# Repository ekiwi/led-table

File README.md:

8x8 RGB LED Table
=================

This project aimed at creating a 8x8 RGB LED Table that
features two controlers:
* a Colorduino from iTead Studio inside the table
* and a custom Main Board featuring an atmega644
  for the control panel

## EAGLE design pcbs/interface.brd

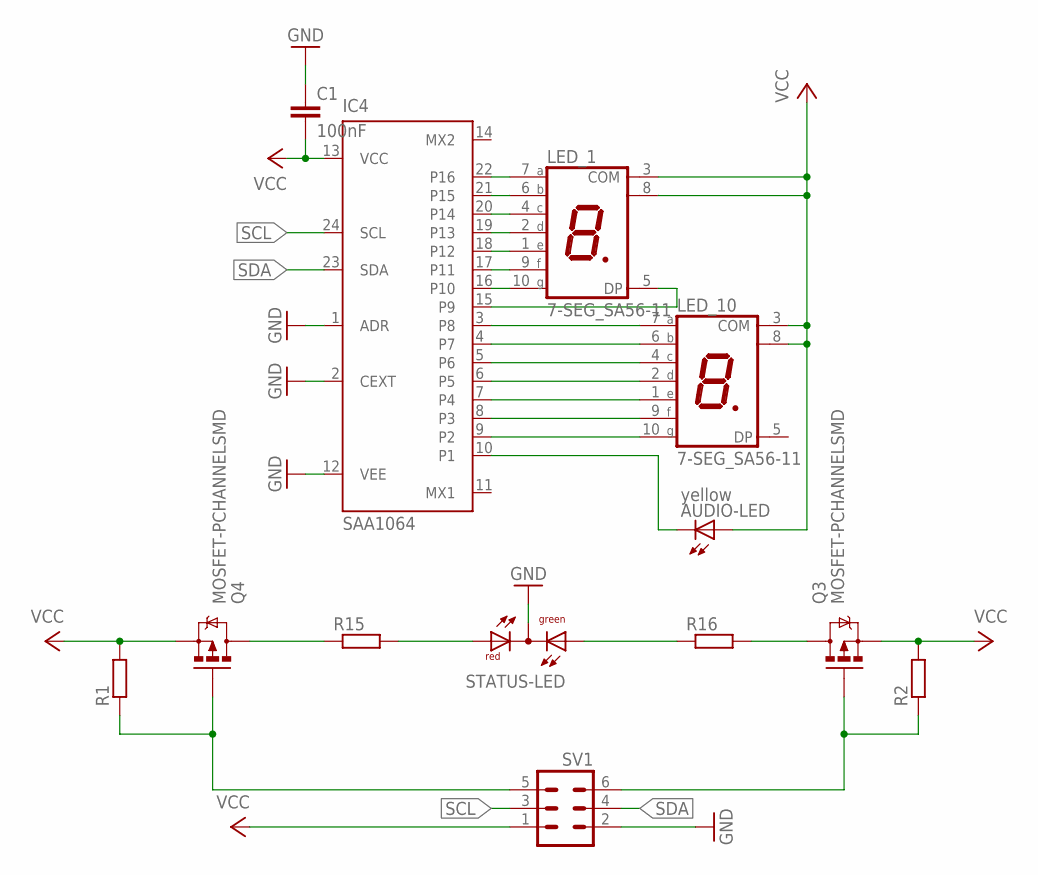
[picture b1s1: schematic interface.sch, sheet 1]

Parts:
AUDIO-LED: yellow; LED10MM
C1: 100nF; C1206
IC4: SAA1064; DIL24-6
LED_1, LED_10: 7-SEG_SA56-11; SA56-11
Q3, Q4: MOSFET-PCHANNELSMD; SOT23-3
R1, R2, R15, R16: R-EU_R1206; R1206
STATUS-LED: DUOLED-RG-C; DUOLED-C-5MM
SV1: ML6SMD2; ML6_SMD2

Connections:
GND: C1.1, IC4.1 (ADR), IC4.2 (CEXT), IC4.12 (VEE), STATUS-LED.C, SV1.2
unnamed: IC4.17 (P11), LED_1.9 (F)
unnamed: IC4.19 (P13), LED_1.2 (D)
unnamed: IC4.21 (P15), LED_1.6 (B)
unnamed: IC4.22 (P16), LED_1.7 (A)
unnamed: IC4.20 (P14), LED_1.4 (C)
unnamed: IC4.18 (P12), LED_1.1 (E)
unnamed: IC4.16 (P10), LED_1.10 (G)
unnamed: IC4.15 (P9), LED_1.5 (DP)
unnamed: AUDIO-LED.K (C), IC4.10 (P1)
unnamed: IC4.3 (P8), LED_10.7 (A)
unnamed: IC4.4 (P7), LED_10.6 (B)
unnamed: IC4.5 (P6), LED_10.4 (C)
unnamed: IC4.6 (P5), LED_10.2 (D)
unnamed: IC4.7 (P4), LED_10.1 (E)
unnamed: IC4.8 (P3), LED_10.9 (F)
unnamed: IC4.9 (P2), LED_10.10 (G)
unnamed: Q4.3 (D), R15.1
unnamed: Q3.3 (D), R16.2
unnamed: R15.2, STATUS-LED.AR
unnamed: R16.1, STATUS-LED.AX (AG)
SCL: IC4.24 (SCL), SV1.3
SDA: IC4.23 (SDA), SV1.4
STATUS_GREEN: Q3.1 (G), R2.1, SV1.6
STATUS_RED: Q4.1 (G), R1.1, SV1.5
VCC: AUDIO-LED.A, C1.2, IC4.13 (VCC), LED_1.3 (COM), LED_1.8 (COM), LED_10.3 (COM), LED_10.8 (COM), Q3.2 (S), Q4.2 (S), R1.2, R2.2, SV1.1

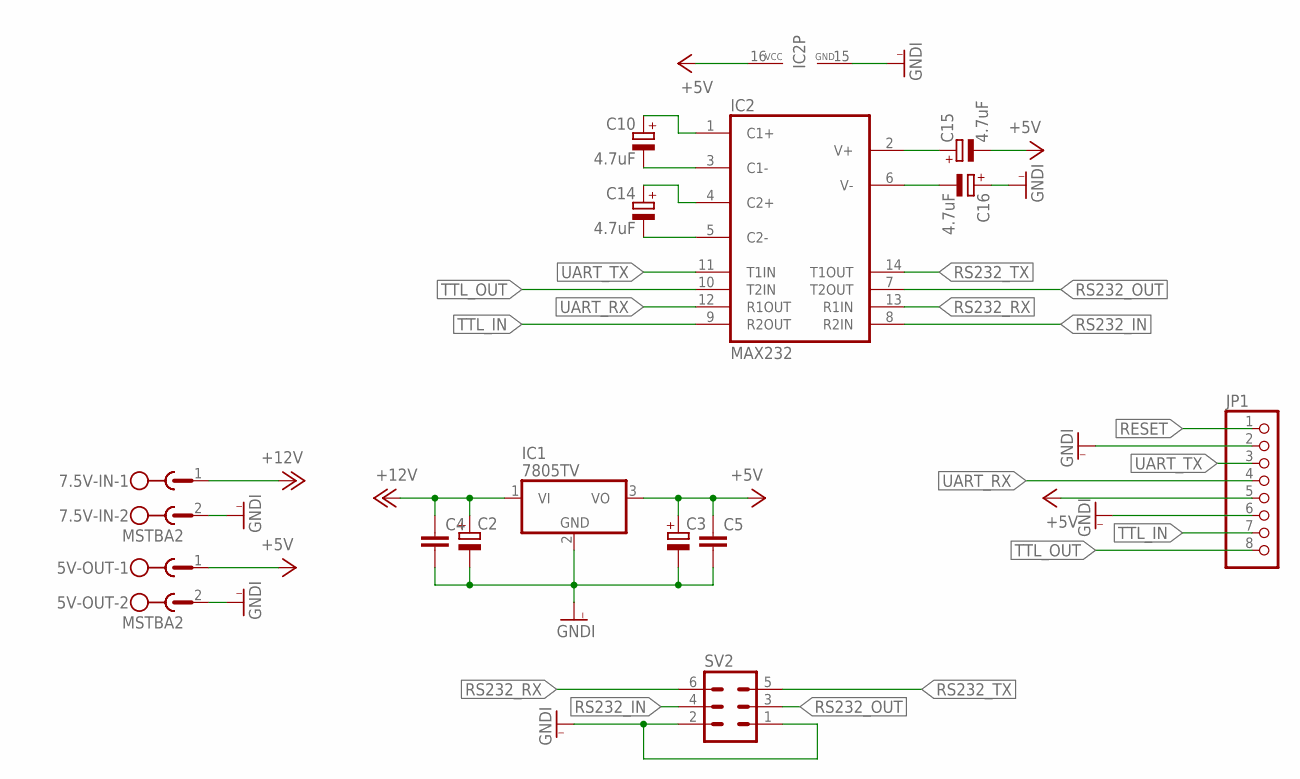
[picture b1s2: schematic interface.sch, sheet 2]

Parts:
5V-OUT, 7.5V-IN: MSTBA2
C2, C3: CPOL-EUE5-10.5; E5-10,5
C4, C5: C-EUC1206; C1206
C10, C14, C15, C16: 4.7uF; E2-5
IC1: 7805TV; TO220V
IC2: MAX232; DIL16
JP1: PINHD-1X8/90; 1X08/90
SV2: ML6

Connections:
+5V: 5V-OUT.1, C3.+, C5.1, C15.-, IC1.3 (VO), IC2.16 (VCC), JP1.5
+12V: 7.5V-IN.1, C2.+, C4.1, IC1.1 (VI)
GNDI: 5V-OUT.2, 7.5V-IN.2, C2.-, C3.-, C4.2, C5.2, C16.+, IC1.2 (GND), IC2.15 (GND), JP1.2, JP1.6, SV2.1, SV2.2
unnamed: C14.+, IC2.4 (C2+)
unnamed: C14.-, IC2.5 (C2-)
unnamed: C10.-, IC2.3 (C1-)
unnamed: C10.+, IC2.1 (C1+)
unnamed: C16.-, IC2.6 (V-)
unnamed: C15.+, IC2.2 (V+)
RESET: JP1.1
RS232_IN: IC2.8 (R2IN), SV2.4
RS232_OUT: IC2.7 (T2OUT), SV2.3
RS232_RX: IC2.13 (R1IN), SV2.6
RS232_TX: IC2.14 (T1OUT), SV2.5
TTL_IN: IC2.9 (R2OUT), JP1.7
TTL_OUT: IC2.10 (T2IN), JP1.8
UART_RX: IC2.12 (R1OUT), JP1.4
UART_TX: IC2.11 (T1IN), JP1.3

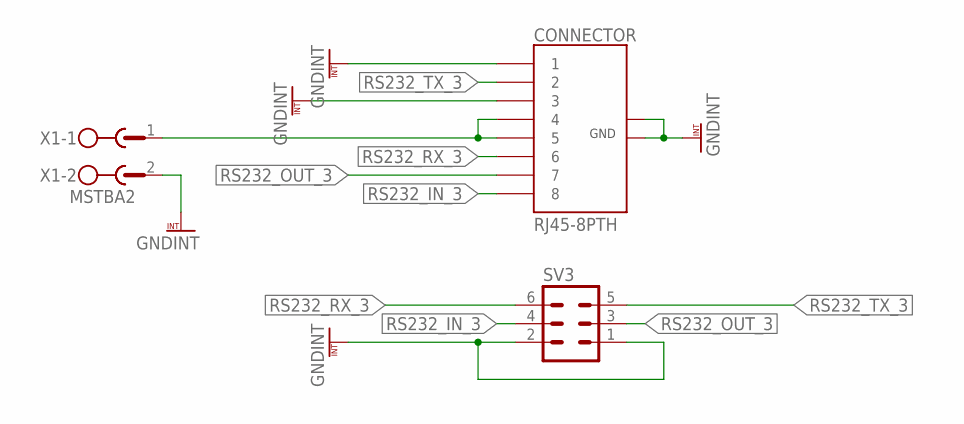
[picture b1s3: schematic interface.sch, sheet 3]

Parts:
CONNECTOR: RJ45-8PTH; RJ45-8
SV3: ML6
X1: MSTBA2

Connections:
GNDINT: CONNECTOR.1, CONNECTOR.3, CONNECTOR.GND_1, CONNECTOR.GND_2, SV3.1, SV3.2, X1.2
RS232_IN_3: CONNECTOR.8, SV3.4
RS232_OUT_3: CONNECTOR.7, SV3.3
RS232_RX_3: CONNECTOR.6, SV3.6
RS232_TX_3: CONNECTOR.2, SV3.5
V_BAT: CONNECTOR.4, CONNECTOR.5, X1.1

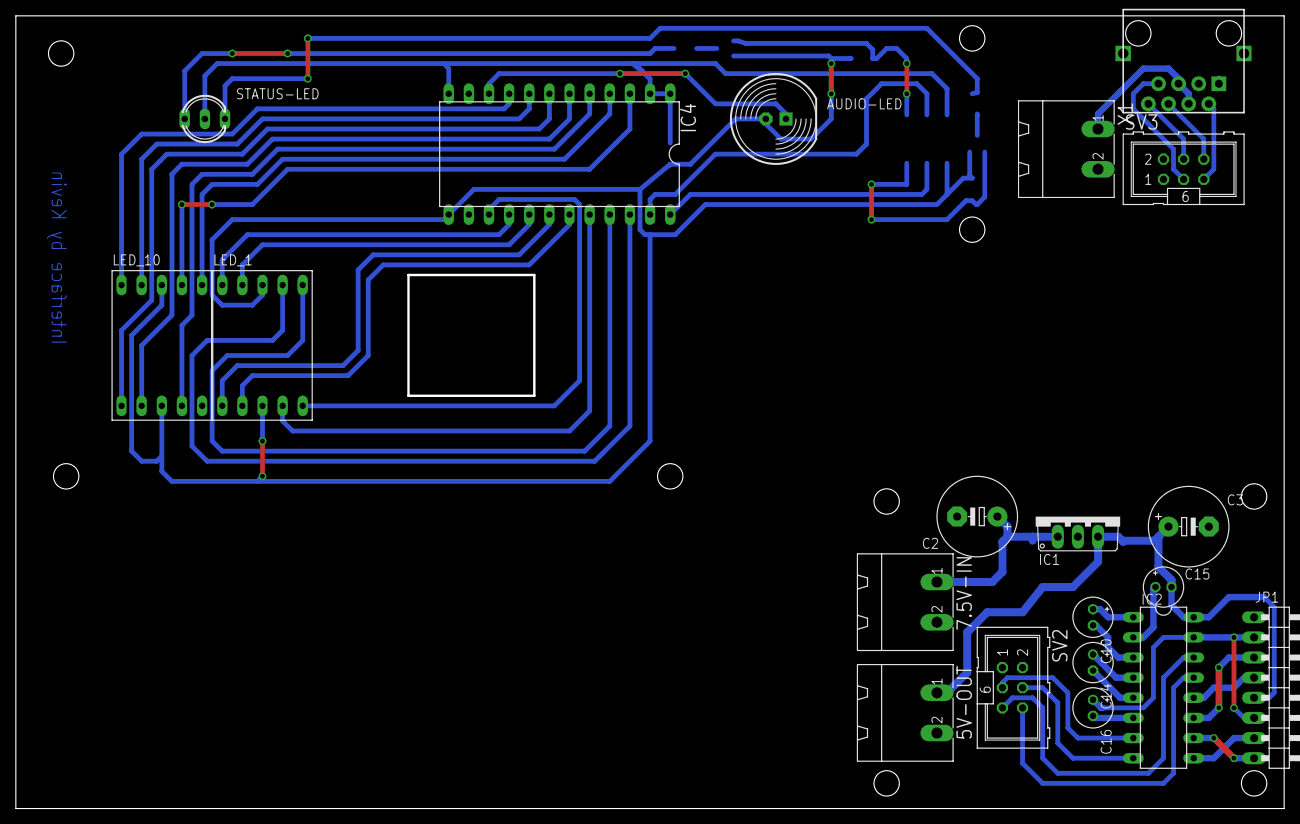
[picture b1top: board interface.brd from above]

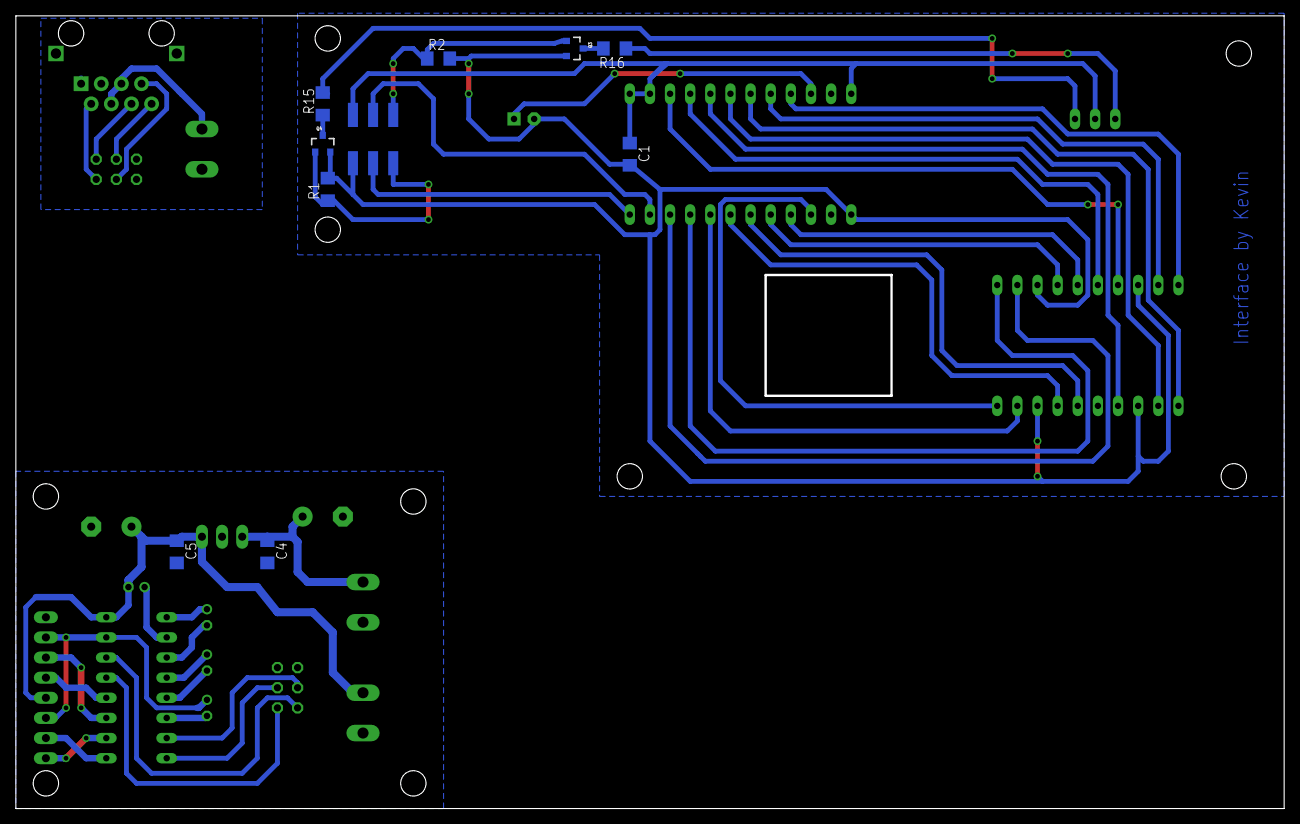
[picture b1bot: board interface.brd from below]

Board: 2 copper layers, 159.7 x 99.7 mm, 30 parts (10 on the bottom side), 49 nets.

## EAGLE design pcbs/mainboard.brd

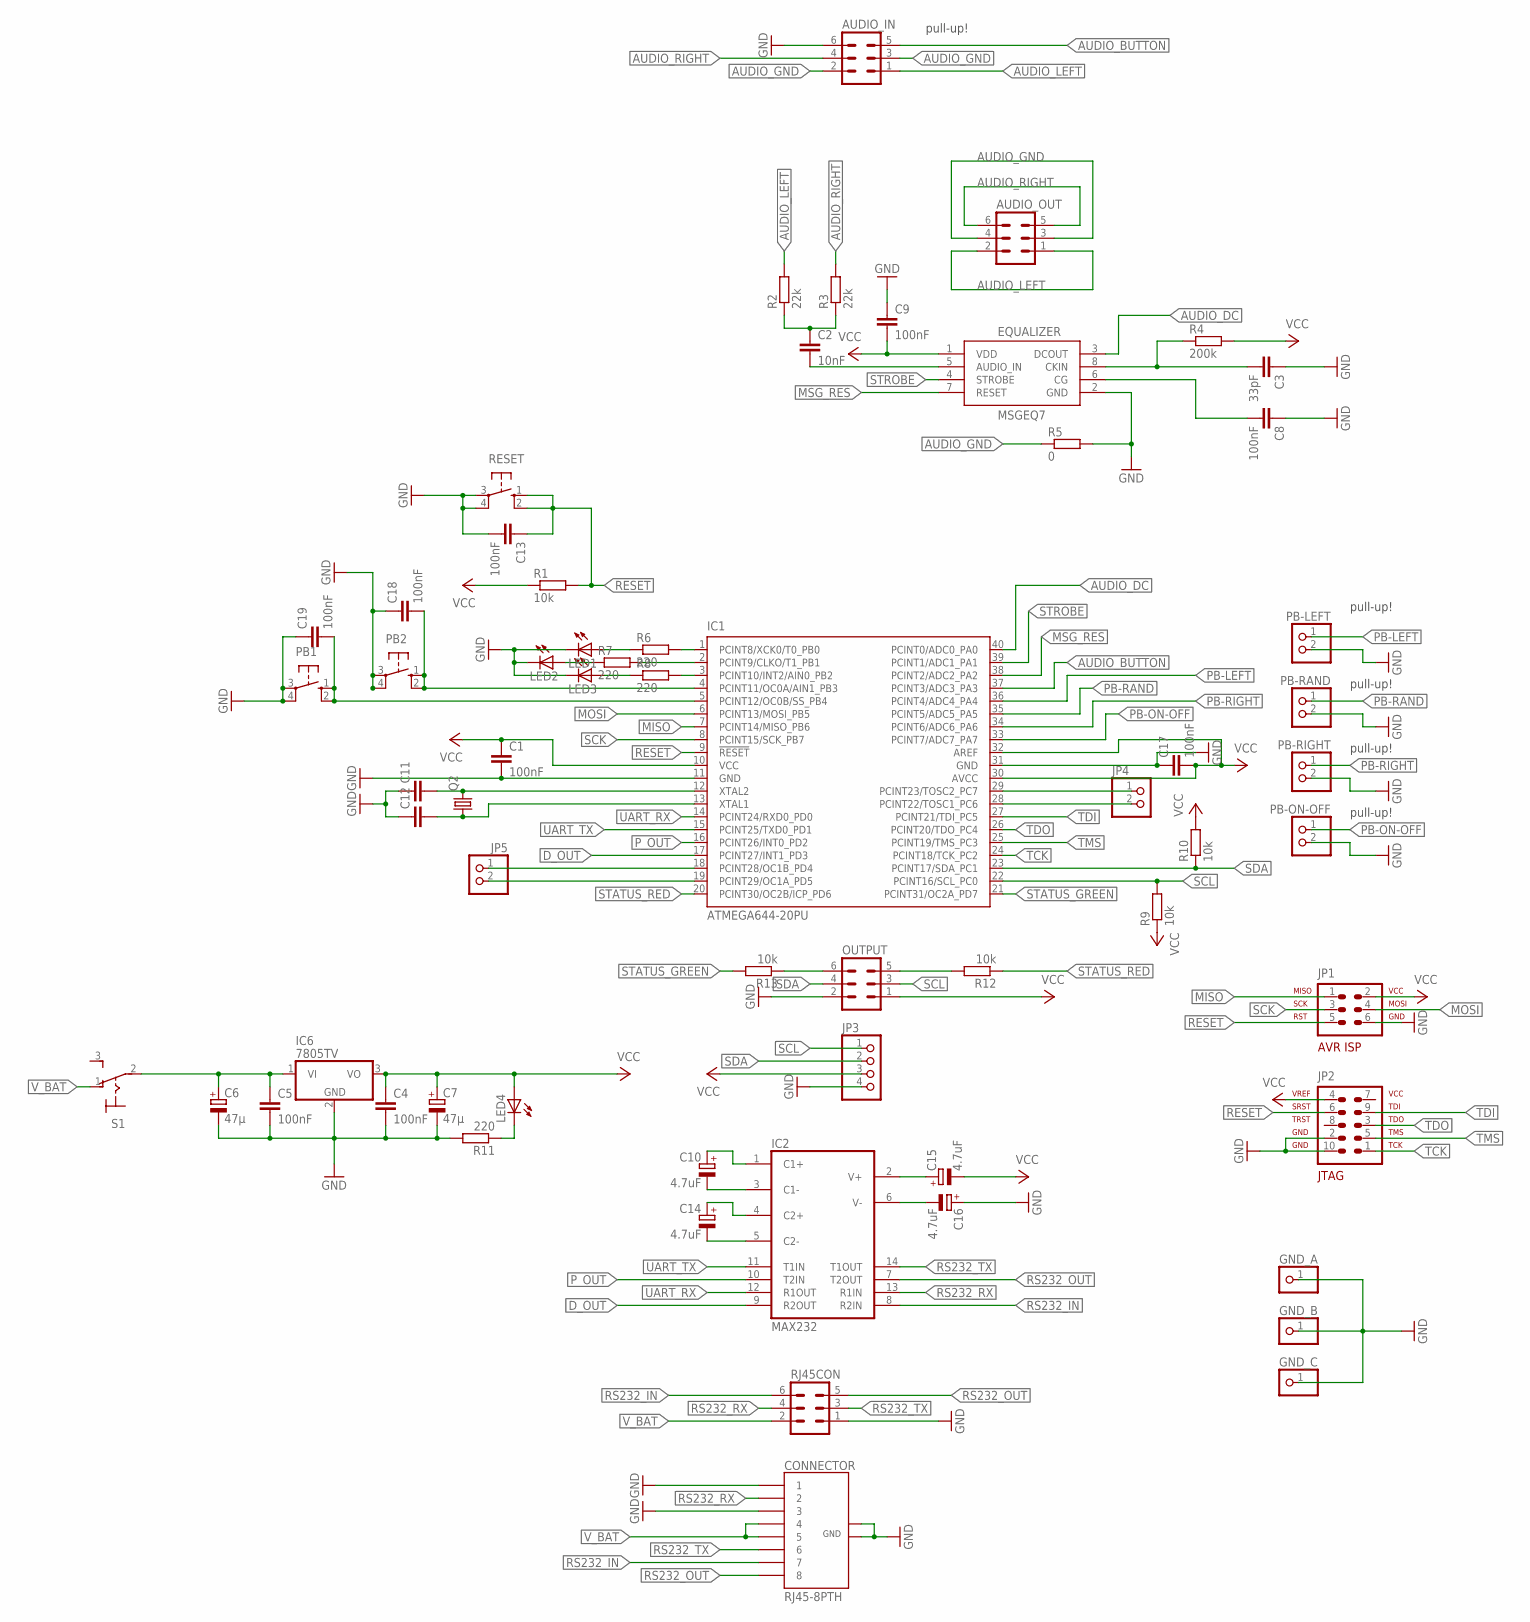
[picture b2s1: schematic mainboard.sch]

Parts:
AUDIO_IN: ML6
AUDIO_OUT: ML6
C1, C4, C5, C8, C9, C13, C17, C18, C19: 100nF; C1206
C2: 10nF; C1206
C3: 33pF; C1206
C6, C7: 47µ; E2,5-6
C10, C14, C15, C16: 4.7uF; E2-5
C11, C12: C-EUC1206; C1206
CONNECTOR: RJ45-8PTH; RJ45-8
EQUALIZER: MSGEQ7; DIL-08
GND_A: PINHD-1X1; 1X01
GND_B: PINHD-1X1; 1X01
GND_C: PINHD-1X1; 1X01
IC1: ATMEGA644-20PU; DIL40
IC2: MAX232; DIL16
IC6: 7805TV; TO220V
JP1: AVR-ISP-6VERT; AVR-ISP-6
JP2: AVR-JTAG-10
JP3: PINHD-1X4; 1X04
JP4, JP5: PINHD-1X2; 1X02
LED1, LED2, LED3, LED4: LED5MM
OUTPUT: ML6
PB1, PB2: 10-XX; B3F-10XX; MPN B3F-1000
PB-LEFT: PINHD-1X2; 1X02
PB-ON-OFF: PINHD-1X2; 1X02
PB-RAND: PINHD-1X2; 1X02
PB-RIGHT: PINHD-1X2; 1X02
Q2: CRYSTALHC49S; HC49/S
R1, R9: 10k; 0207/10
R2, R3: 22k; 0207/10
R4: 200k; 0207/10
R5: 0; M1206
R6, R7, R8, R11: 220; 0207/10
R10, R13: 10k; 0207/12
R12: 10k; 0207/15
RESET: 10-XX; B3F-10XX
RJ45CON: ML6
S1: M9040P

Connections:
AUDIO_BUTTON: AUDIO_IN.5, IC1.37 (PCINT3/ADC3_PA3)
AUDIO_DC: EQUALIZER.3 (DCOUT), IC1.40 (PCINT0/ADC0_PA0)
AUDIO_GND: AUDIO_IN.2, AUDIO_IN.3, AUDIO_OUT.3, AUDIO_OUT.4, R5.1
AUDIO_LEFT: AUDIO_IN.1, AUDIO_OUT.1, AUDIO_OUT.2, R2.2
AUDIO_RIGHT: AUDIO_IN.4, AUDIO_OUT.5, AUDIO_OUT.6, R3.2
D_OUT: IC1.17 (PCINT27/INT1_PD3), IC2.9 (R2OUT)
FJKSABFJSD: C5.1, C6.+, IC6.1 (VI), S1.2
GND: AUDIO_IN.6, C1.2, C3.1, C4.2, C5.2, C6.-, C7.-, C8.1, C9.1, C11.1, C12.1, C13.2, C16.+, C17.1, C18.1, C19.1, CONNECTOR.1, CONNECTOR.3, CONNECTOR.GND_1, CONNECTOR.GND_2, EQUALIZER.2 (GND), GND_A.1, GND_B.1, GND_C.1, IC1.11 (GND), IC1.31 (GND), IC2.15 (GND), IC6.2 (GND), JP1.6, JP2.2, JP2.10, JP3.4, LED1.K (C), LED2.K (C), LED3.K (C), OUTPUT.2, PB1.3, PB1.4 (P1), PB2.3, PB2.4 (P1), PB-LEFT.2, PB-ON-OFF.2, PB-RAND.2, PB-RIGHT.2, R5.2, R11.2, RESET.3, RESET.4 (P1), RJ45CON.1
MISO: IC1.7 (PCINT14/MISO_PB6), JP1.1
MOSI: IC1.6 (PCINT13/MOSI_PB5), JP1.4
MSG_RES: EQUALIZER.7 (RESET), IC1.38 (PCINT2/ADC2_PA2)
unnamed: C2.2, EQUALIZER.5 (AUDIO_IN)
unnamed: C2.1, R2.1, R3.1
unnamed: C3.2, EQUALIZER.8 (CKIN), R4.1
unnamed: C14.+, IC2.4 (C2+)
unnamed: C8.2, EQUALIZER.6 (CG)
unnamed: C14.-, IC2.5 (C2-)
unnamed: C10.-, IC2.3 (C1-)
unnamed: C10.+, IC2.1 (C1+)
unnamed: C16.-, IC2.6 (V-)
unnamed: C15.+, IC2.2 (V+)
unnamed: LED1.A, R6.1
unnamed: IC1.1 (PCINT8/XCK0/T0_PB0), R6.2
unnamed: IC1.2 (PCINT9/CLKO/T1_PB1), R7.2
unnamed: LED2.A, R7.1
unnamed: IC1.3 (PCINT10/INT2/AIN0_PB2), R8.2
unnamed: C11.2, IC1.12 (XTAL2), Q2.2
unnamed: C12.2, IC1.13 (XTAL1), Q2.1
unnamed: LED3.A, R8.1
unnamed: LED4.K (C), R11.1
unnamed: C18.2, IC1.4 (PCINT11/OC0A/AIN1_PB3), PB2.1 (S), PB2.2 (S1)
unnamed: IC1.28 (PCINT22/TOSC1_PC6), JP4.2
unnamed: IC1.29 (PCINT23/TOSC2_PC7), JP4.1
unnamed: OUTPUT.5, R12.2
unnamed: C19.2, IC1.5 (PCINT12/OC0B/SS_PB4), PB1.1 (S), PB1.2 (S1)
unnamed: OUTPUT.6, R13.1
unnamed: IC1.18 (PCINT28/OC1B_PD4), JP5.1
unnamed: IC1.19 (PCINT29/OC1A_PD5), JP5.2
PB-LEFT: IC1.36 (PCINT4/ADC4_PA4), PB-LEFT.1
PB-ON-OFF: IC1.33 (PCINT7/ADC7_PA7), PB-ON-OFF.1
PB-RAND: IC1.35 (PCINT5/ADC5_PA5), PB-RAND.1
PB-RIGHT: IC1.34 (PCINT6/ADC6_PA6), PB-RIGHT.1
P_OUT: IC1.16 (PCINT26/INT0_PD2), IC2.10 (T2IN)
RESET: C13.1, IC1.9 (!RESET), JP1.5, JP2.6, R1.2, RESET.1 (S), RESET.2 (S1)
RS232_IN: CONNECTOR.7, IC2.8 (R2IN), RJ45CON.6
RS232_OUT: CONNECTOR.8, IC2.7 (T2OUT), RJ45CON.5
RS232_RX: CONNECTOR.2, IC2.13 (R1IN), RJ45CON.4
RS232_TX: CONNECTOR.6, IC2.14 (T1OUT), RJ45CON.3
SCK: IC1.8 (PCINT15/SCK_PB7), JP1.3
SCL: IC1.22 (PCINT16/SCL_PC0), JP3.1, OUTPUT.3, R9.2
SDA: IC1.23 (PCINT17/SDA_PC1), JP3.2, OUTPUT.4, R10.1
STATUS_GREEN: IC1.21 (PCINT31/OC2A_PD7), R13.2
STATUS_RED: IC1.20 (PCINT30/OC2B/ICP_PD6), R12.1
STROBE: EQUALIZER.4 (STROBE), IC1.39 (PCINT1/ADC1_PA1)
TCK: IC1.24 (PCINT18/TCK_PC2), JP2.1
TDI: IC1.27 (PCINT21/TDI_PC5), JP2.9
TDO: IC1.26 (PCINT20/TDO_PC4), JP2.3
TMS: IC1.25 (PCINT19/TMS_PC3), JP2.5
UART_RX: IC1.14 (PCINT24/RXD0_PD0), IC2.12 (R1OUT)
UART_TX: IC1.15 (PCINT25/TXD0_PD1), IC2.11 (T1IN)
VCC: C1.1, C4.1, C7.+, C9.2, C15.-, C17.2, EQUALIZER.1 (VDD), IC1.10 (VCC), IC1.30 (AVCC), IC1.32 (AREF), IC2.16 (VCC), IC6.3 (VO), JP1.2, JP2.4, JP3.3, LED4.A, OUTPUT.1, R1.1, R4.2, R9.1, R10.2
V_BAT: CONNECTOR.4, CONNECTOR.5, RJ45CON.2, S1.1 (O)

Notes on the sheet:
pull-up!

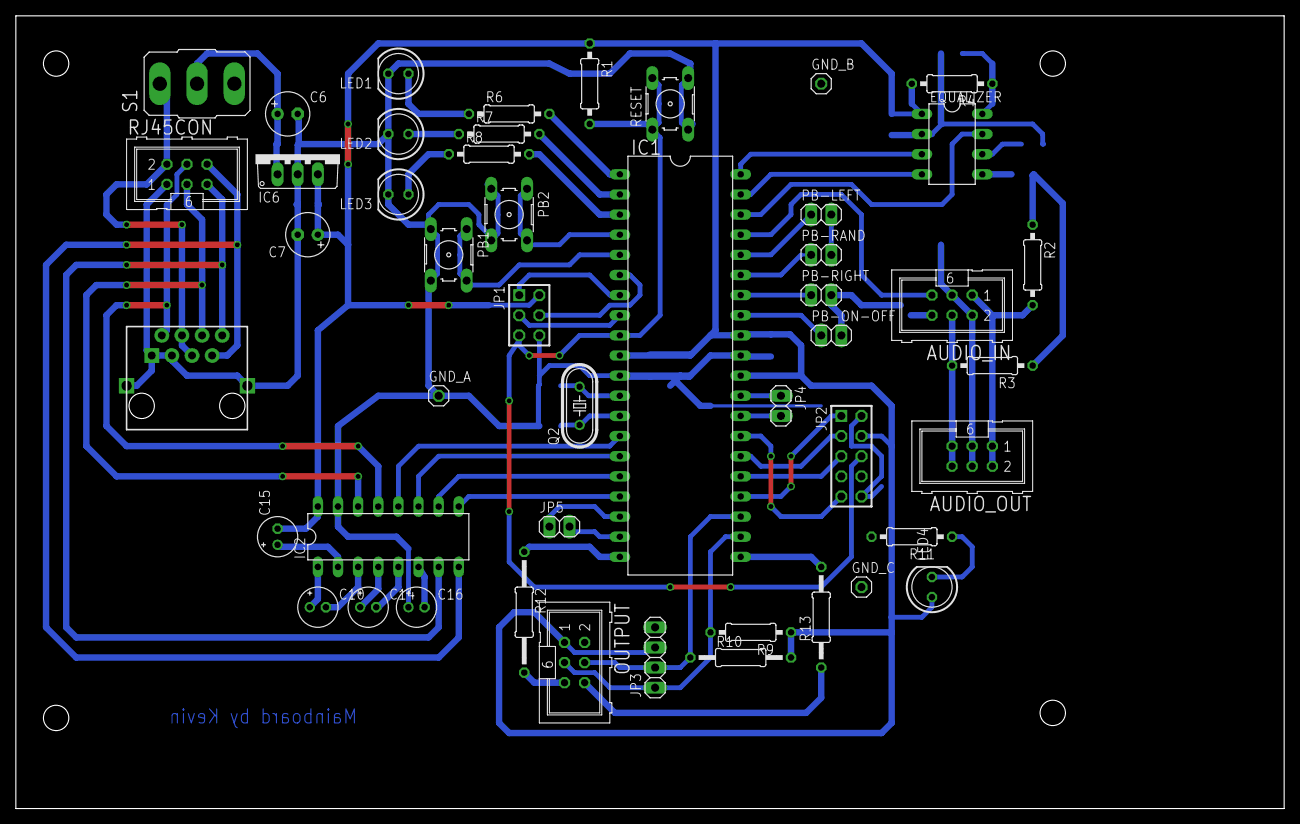
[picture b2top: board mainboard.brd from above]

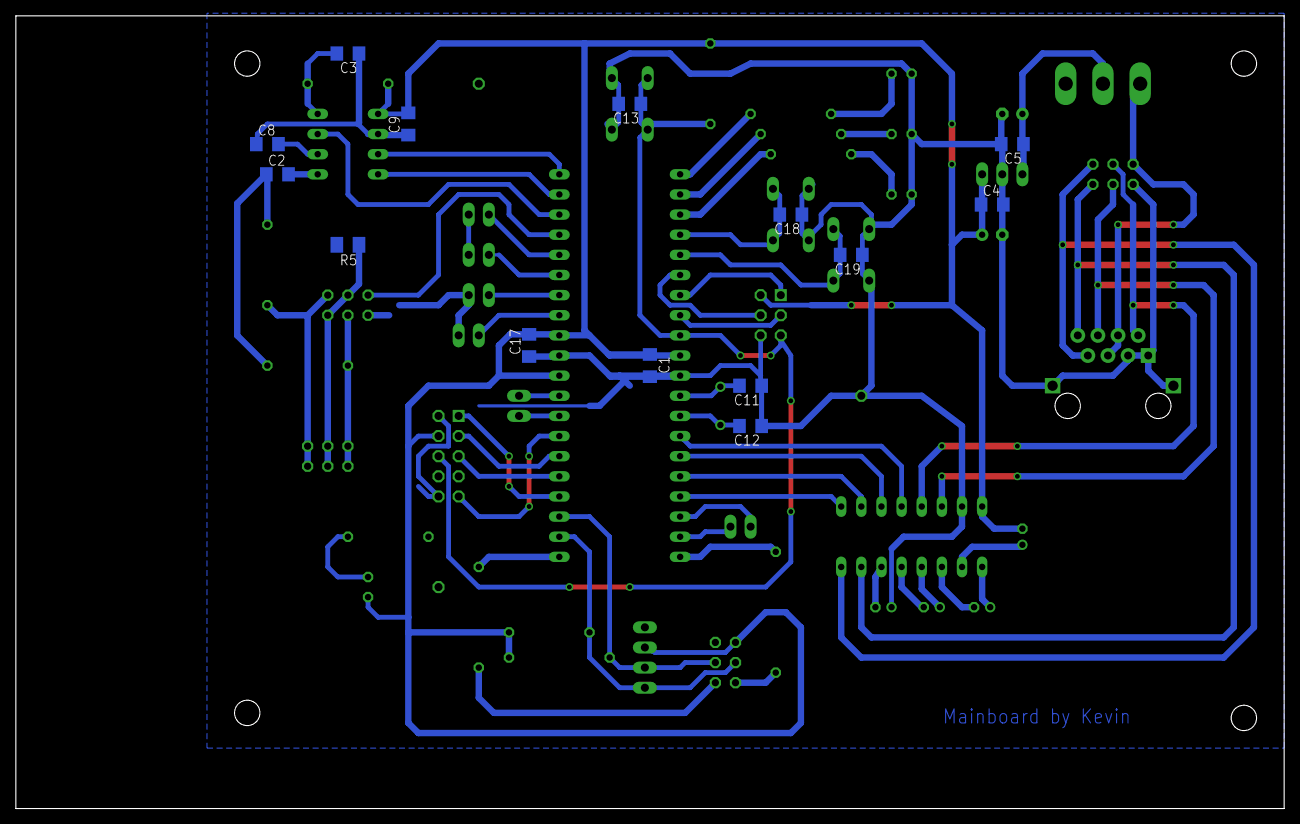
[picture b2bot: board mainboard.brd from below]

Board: 2 copper layers, 160.0 x 100.0 mm, 62 parts (14 on the bottom side), 62 nets.

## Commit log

2012-09-24 .gitignore: Added rudimentary file for C, qmake and gedit backups.
2012-09-24 Simulator: Added qt Creator Project WARNING: Not working right now!
2012-09-24 Animations: Added all available animations
2012-09-24 Simulator: simplified name
2012-09-24 Control Panel: added initial firmware
2012-09-24 gitignore: Added some eclipse files
2012-09-29 .gitignore: Added exclude for user specific qt files and Release folder
2012-09-29 Control Panel: Adjusted the project files to make it build in eclipse.
2012-09-29 Colorduino Firware added.
2012-09-29 Simulator: Changed paths to reflect animation folder moved to ../animations
2012-09-29 Simulator: Now builds and runs as expected.
2012-09-30 README: Added initial project description.
2012-09-30 PCB: Added custom control panel board created with eagle CAD.
2012-09-30 .gitignore: Added ignore for eagle backups
2012-09-30 Windows: Changed compile mode to GNU specific C and added some Windows specific file ignores to gitignore. Simulator compiles and runs, but still has some issues.
2012-11-06 GPLv2: Started putting GLPv2 head comments into files.
2012-11-23 Documentation: Added German Getting Started Guide Not finished.
2012-11-23 Changed ani_default to easy getting started animation.
2012-11-23 Documentation: DE Getting Started: Added how to change animation.
    Added a Chapter on how to modify the default animation to show
    a rectangle slowly moving from the left to the right side of the screen.

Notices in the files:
parts and their libraries:
SparkFun: Licensing: CC v3.0 Share-Alike You are welcome to use this library for commercial purposes.
